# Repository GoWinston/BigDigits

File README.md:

# The Big Board

This is an Arduino powered system to allow the construction of giant seven segment displays, up to 50V 0.5A per segment.

The library workes with any Arduino using the SPI protocol, allowing a 4 digit display (32 segements) to be remotely connected via a single ethernet cable.

Two PCB designs are included, one with four digits on one board and another with a single digit per board.  

The hardware and library support four channels. 

<hr>

Boards are availible at OshPark <br>
4 Channel: https://oshpark.com/shared_projects/9ZOlH1Lw <br>
Digikey parts list [here](https://github.com/GoWinston/BigDigits/blob/master/PCB's/4%20Digit%20PCB%20Materials%20Digikey.csv)<br>
<br>
1 Channel: https://oshpark.com/shared_projects/VTMd3b0f <br>
Digikey parts list [here](https://github.com/GoWinston/BigDigits/blob/master/PCB's/1%20Digit%20PCB%20Materials%20Digikey.csv)<br>

<hr>

Connect to the Arduino with a standard ethernet cable and the SparkFun RJ45 Breakout <br>
https://www.sparkfun.com/products/716 <br>
<br>
```
Ethernet | Arduino | Assignment
    1         13      Clock - SCK - SHCP
    2         11      Data - MOSI - DS
    3         9       Digit D  X---  Thousands
    4         6       Digit A  ---X  Units
    5         8       Digit C  -X--  Hundreds
    6         7       Digit B  --X-  Tens
    7         +5      VCC
    8         GND     GND
```
<hr>

The power for the big displays goes directly into the PCBs and is seperate from the logic power on the Arduino which travels over the ethernet cable<br>
<br>
Power each segement from V+ --> LED segment lights --> Control Board <br>
<hr>

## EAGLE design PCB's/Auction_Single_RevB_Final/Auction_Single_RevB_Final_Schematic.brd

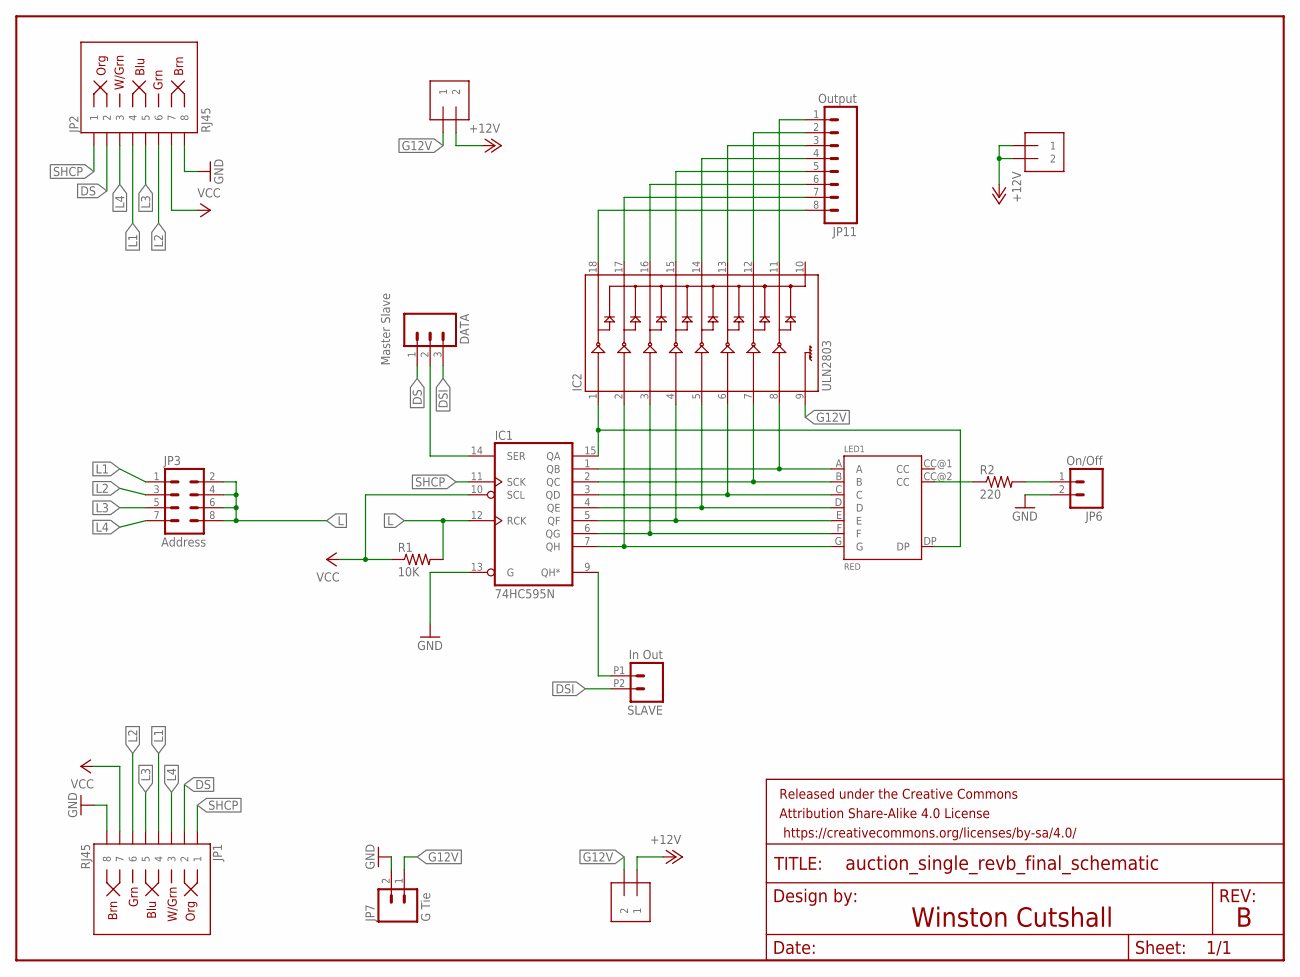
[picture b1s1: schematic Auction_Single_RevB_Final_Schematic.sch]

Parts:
DATA: Master Slave; 1X03; MPN 2211S-03G
FRAME1: FRAME-LETTER; CREATIVE_COMMONS
IC1: 74HC595N; DIL16; MPN SN74HC595N
IC2: ULN2803; DIL18; MPN ULN2803A
JP1, JP2: RJ45; RJ45-8; MPN 54602-908LF
JP3: Address; 2X4; MPN M20-9980446
JP6: On/Off; 1X02; MPN 2211S-02G
JP7: G Tie; 1X02; MPN 2211S-02G
JP8, JP9, JP10: 1X2-3.5MM; MPN 1776275-2
JP11: Output; SCREWTERMINAL-3.5MM-8; MPN 20020327-C081B01LF
LED1: RED; HDSP-C3X3
R1: 10K; AXIAL-0.3EZ; MPN MCF 0.25W 10K
R2: 220; AXIAL-0.3EZ; MPN MCF 0.25W 220R
SLAVE: In Out; 1X02_2.54_SCREWTERM; MPN 282834-2

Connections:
+12V: JP8.1, JP9.2, JP10.1, JP10.2
A: IC1.1 (QB), IC2.8, LED1.A
AA: IC2.11, JP11.1
B: IC1.2 (QC), IC2.7, LED1.B
BB: IC2.12, JP11.2
C: IC1.3 (QD), IC2.6, LED1.C
CC: IC2.13, JP11.3
D: IC1.4 (QE), IC2.5, LED1.D
DD: IC2.14, JP11.4
DIP_SEG: JP6.1, R2.P$2 (2)
DP: IC1.15 (QA), IC2.1, LED1.DP
DPA: IC2.18, JP11.8
DS: DATA.1, JP1.2, JP2.2
DSF: DATA.2, IC1.14 (SER)
DSI: DATA.3, SLAVE.P2 (2)
E: IC1.5 (QF), IC2.4, LED1.E
EE: IC2.15, JP11.5
F: IC1.6 (QG), IC2.3, LED1.F
FF: IC2.16, JP11.6
G: IC1.7 (QH), IC2.2, LED1.G
G12V: IC2.9, JP7.1, JP8.2, JP9.1
GG: IC2.17, JP11.7
GND: IC1.8 (GND), IC1.13 (G), JP1.8, JP2.8, JP6.2, JP7.2
L: IC1.12 (RCK), JP3.2, JP3.4, JP3.6, JP3.8, R1.P$2 (2)
L1: JP1.4, JP2.4, JP3.1
L2: JP1.6, JP2.6, JP3.3
L3: JP1.5, JP2.5, JP3.5
L4: JP1.3, JP2.3, JP3.7
unnamed: LED1.CC@2 (CC), R2.P$1 (1)
unnamed: IC1.9 (QH*), SLAVE.P1 (1)
SHCP: IC1.11 (SCK), JP1.1, JP2.1
VCC: IC1.10 (SCL), IC1.16 (VCC), JP1.7, JP2.7, R1.P$1 (1)

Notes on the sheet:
Winston Cutshall

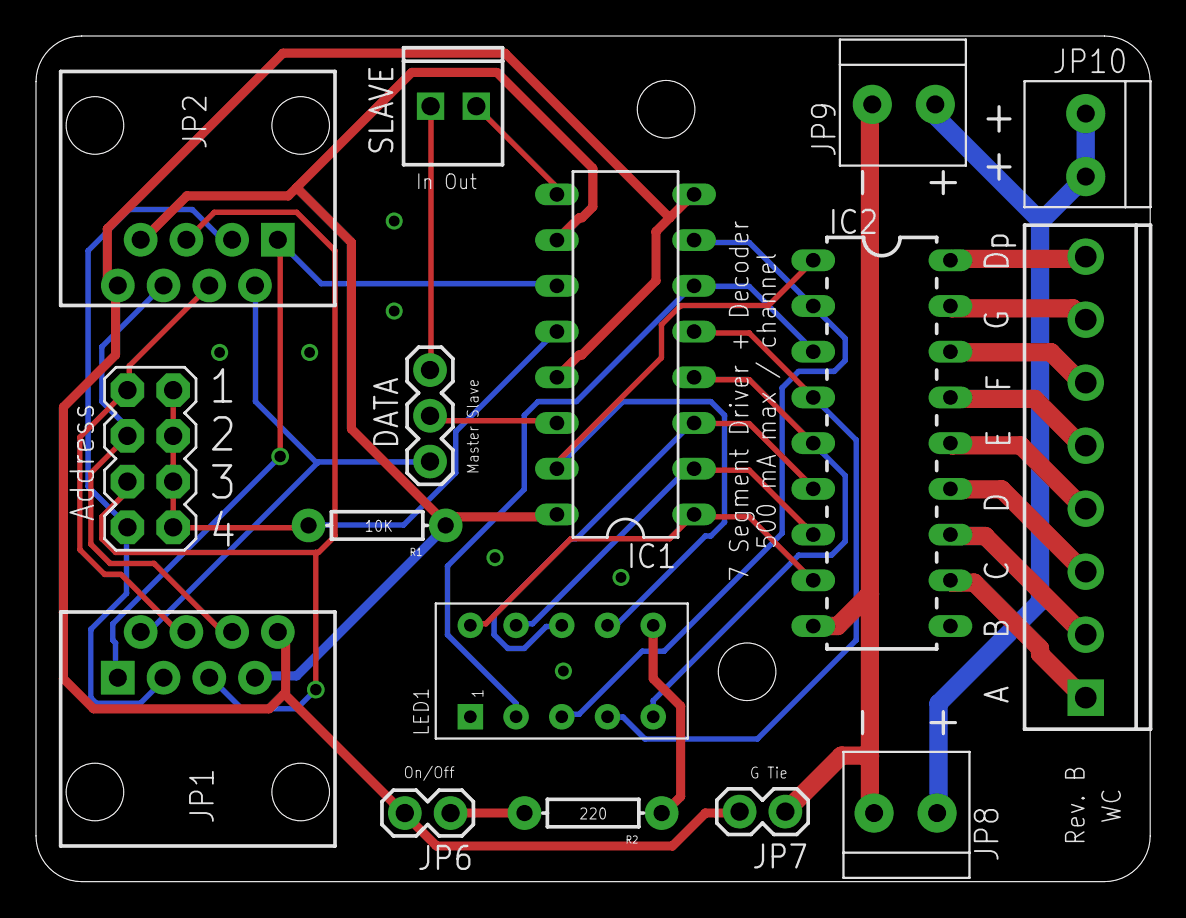
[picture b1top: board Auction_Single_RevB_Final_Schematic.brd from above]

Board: 2 copper layers, 61.9 x 47.0 mm, 17 parts (0 on the bottom side), 32 nets.

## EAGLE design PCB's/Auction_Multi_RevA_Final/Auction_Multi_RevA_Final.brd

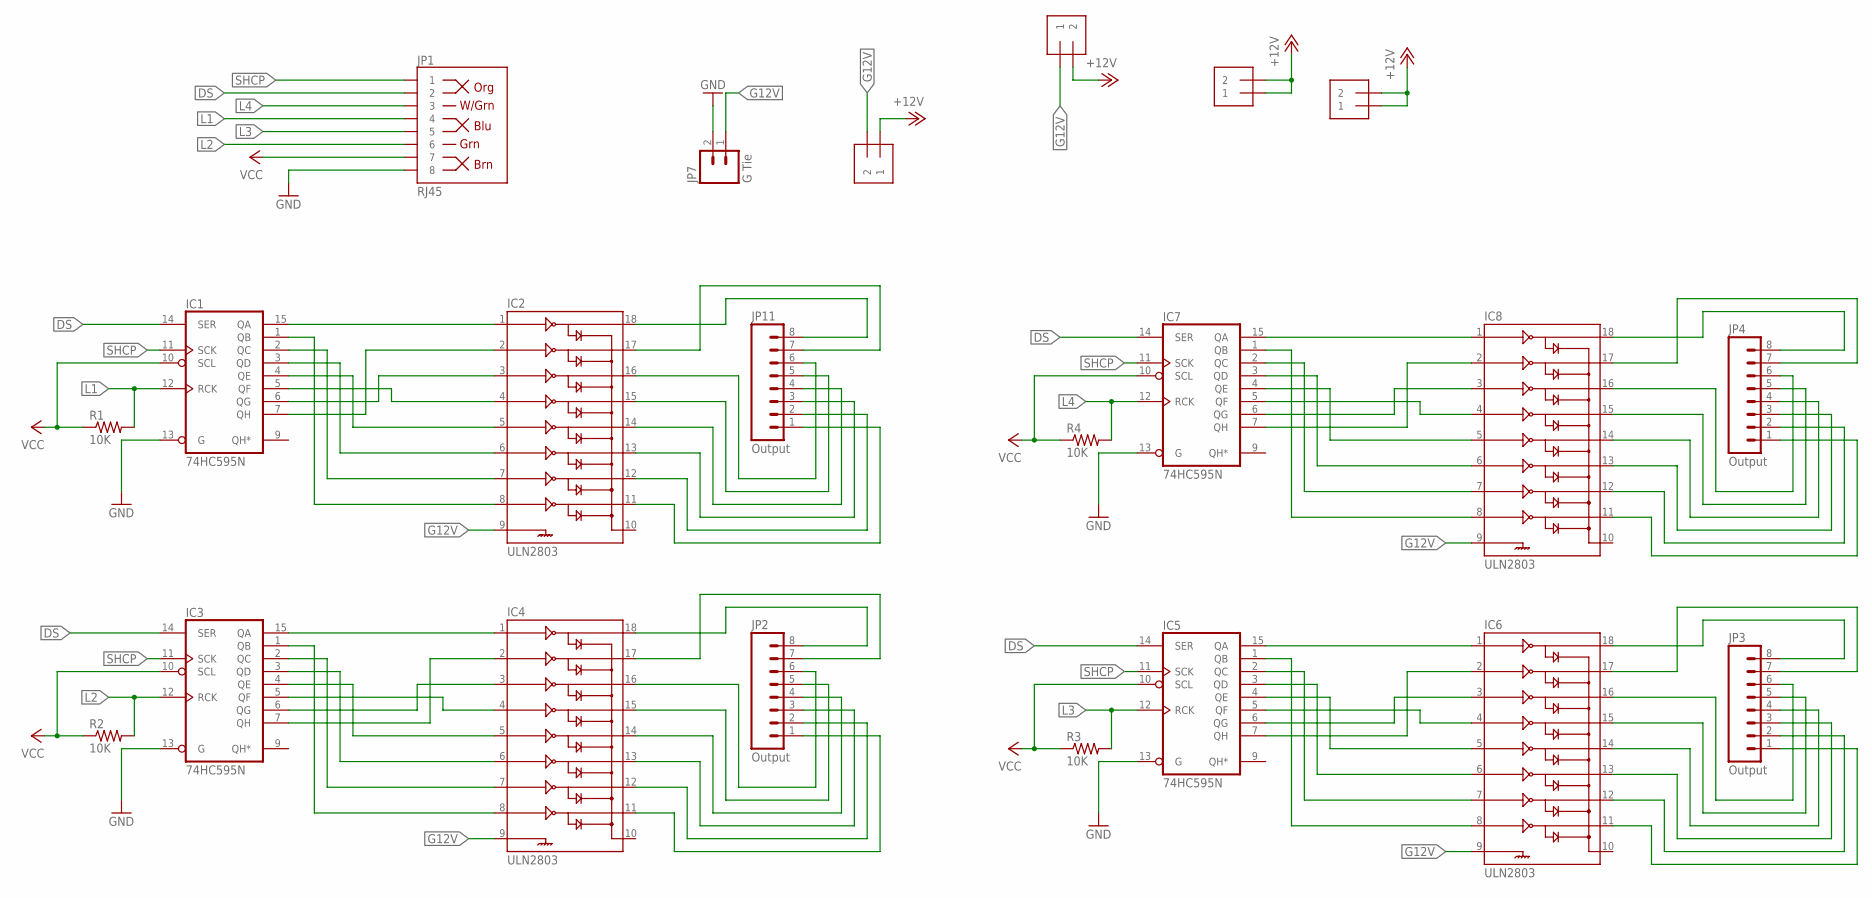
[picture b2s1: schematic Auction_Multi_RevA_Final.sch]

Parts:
IC1, IC3, IC5, IC7: 74HC595N; DIL16; MPN SN74HC595N
IC2, IC4, IC6, IC8: ULN2803; DIL18; MPN ULN2803A
JP1: RJ45; RJ45-8; MPN 54602-908LF
JP2, JP3, JP4, JP11: Output; SCREWTERMINAL-3.5MM-8; MPN 20020327-C081B01LF
JP5, JP8, JP9, JP10: 1X2-3.5MM; MPN 1776275-2
JP7: G Tie; 1X02; MPN 2211S-02G
R1, R2, R3, R4: 10K; AXIAL-0.3EZ; MPN MCF 0.25W 10K

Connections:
+12V: JP5.1, JP5.2, JP8.1, JP9.2, JP10.1, JP10.2
A: IC1.1 (QB), IC2.8
A3: IC7.1 (QB), IC8.8
AA: IC2.11, JP11.1
AA1: IC4.11, JP2.1
AA2: IC6.11, JP3.1
AA3: IC8.11, JP4.1
B3: IC7.2 (QC), IC8.7
BB: IC2.12, JP11.2
BB1: IC4.12, JP2.2
BB2: IC6.12, JP3.2
BB3: IC8.12, JP4.2
C3: IC7.3 (QD), IC8.6
CC: IC2.13, JP11.3
CC1: IC4.13, JP2.3
CC2: IC6.13, JP3.3
CC3: IC8.13, JP4.3
D3: IC7.4 (QE), IC8.5
DD: IC2.14, JP11.4
DD1: IC4.14, JP2.4
DD2: IC6.14, JP3.4
DD3: IC8.14, JP4.4
DP: IC1.15 (QA), IC2.1
DP1: IC3.15 (QA), IC4.1
DP2: IC5.15 (QA), IC6.1
DP3: IC7.15 (QA), IC8.1
DPA: IC2.18, JP11.8
DPA1: IC4.18, JP2.8
DPA2: IC6.18, JP3.8
DPA3: IC8.18, JP4.8
DS: IC1.14 (SER), IC3.14 (SER), IC5.14 (SER), IC7.14 (SER), JP1.2
E1: IC3.5 (QF), IC4.4
E2: IC5.5 (QF), IC6.4
E3: IC7.5 (QF), IC8.4
EE: IC2.15, JP11.5
EE1: IC4.15, JP2.5
EE2: IC6.15, JP3.5
EE3: IC8.15, JP4.5
F: IC1.6 (QG), IC2.3
F1: IC3.6 (QG), IC4.3
F2: IC5.6 (QG), IC6.3
F3: IC7.6 (QG), IC8.3
FF: IC2.16, JP11.6
FF1: IC4.16, JP2.6
FF2: IC6.16, JP3.6
FF3: IC8.16, JP4.6
G: IC1.7 (QH), IC2.2
G1: IC3.7 (QH), IC4.2
G2: IC5.7 (QH), IC6.2
G3: IC7.7 (QH), IC8.2
G12V: IC2.9, IC4.9, IC6.9, IC8.9, JP7.1, JP8.2, JP9.1
GG: IC2.17, JP11.7
GG1: IC4.17, JP2.7
GG2: IC6.17, JP3.7
GG3: IC8.17, JP4.7
GND: IC1.8 (GND), IC1.13 (G), IC3.8 (GND), IC3.13 (G), IC5.8 (GND), IC5.13 (G), IC7.8 (GND), IC7.13 (G), JP1.8, JP7.2
L1: IC1.12 (RCK), JP1.4, R1.P$2 (2)
L2: IC3.12 (RCK), JP1.6, R2.P$2 (2)
L3: IC5.12 (RCK), JP1.5, R3.P$2 (2)
L4: IC7.12 (RCK), JP1.3, R4.P$2 (2)
unnamed: IC3.4 (QE), IC4.5
unnamed: IC1.2 (QC), IC2.7
unnamed: IC1.4 (QE), IC2.5
unnamed: IC1.3 (QD), IC2.6
unnamed: IC1.5 (QF), IC2.4
unnamed: IC3.3 (QD), IC4.6
unnamed: IC3.2 (QC), IC4.7
unnamed: IC3.1 (QB), IC4.8
unnamed: IC5.1 (QB), IC6.8
unnamed: IC5.2 (QC), IC6.7
unnamed: IC5.3 (QD), IC6.6
unnamed: IC5.4 (QE), IC6.5
SHCP: IC1.11 (SCK), IC3.11 (SCK), IC5.11 (SCK), IC7.11 (SCK), JP1.1
VCC: IC1.10 (SCL), IC1.16 (VCC), IC3.10 (SCL), IC3.16 (VCC), IC5.10 (SCL), IC5.16 (VCC), IC7.10 (SCL), IC7.16 (VCC), JP1.7, R1.P$1 (1), R2.P$1 (1), R3.P$1 (1), R4.P$1 (1)

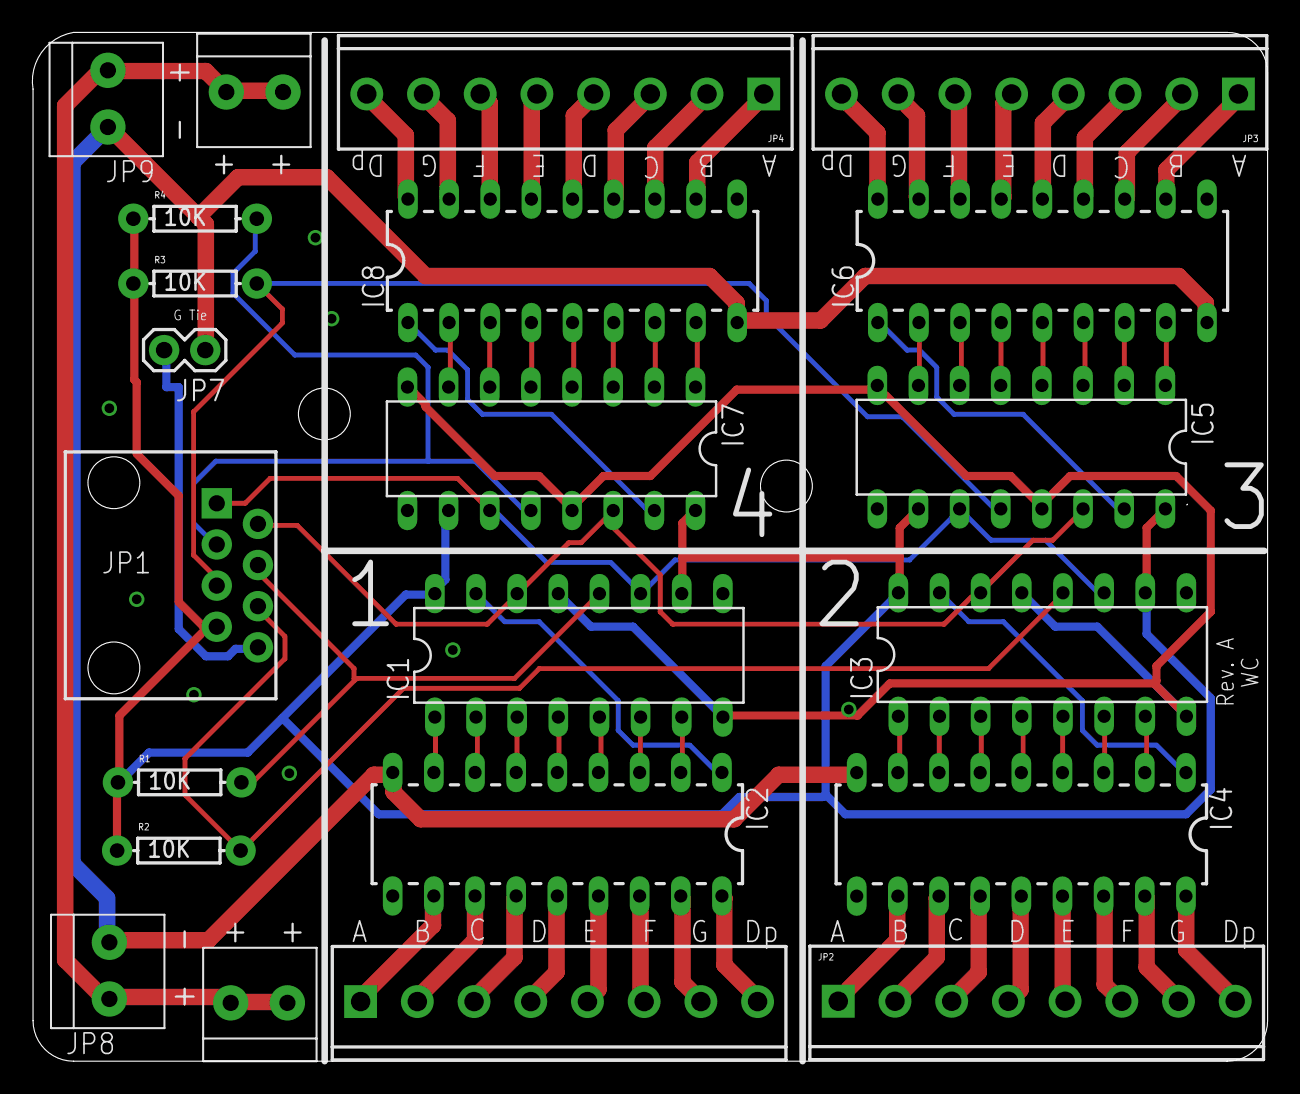
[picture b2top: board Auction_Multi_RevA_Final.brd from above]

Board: 2 copper layers, 76.2 x 63.5 mm, 22 parts (0 on the bottom side), 74 nets.

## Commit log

2016-01-21 Uploading Source Files
2016-01-21 updating files
2016-01-21 Updating PCB Files

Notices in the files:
parts and their libraries:
SparkFun-Connectors: Licensing: Creative Commons ShareAlike 4.0 International - https://creativecommons.org/licenses/by-sa/4.0
SparkFun-Aesthetics: Released under the Creative Commons Attribution Share-Alike 4.0 License
SparkFun-Aesthetics: https://creativecommons.org/licenses/by-sa/4.0
